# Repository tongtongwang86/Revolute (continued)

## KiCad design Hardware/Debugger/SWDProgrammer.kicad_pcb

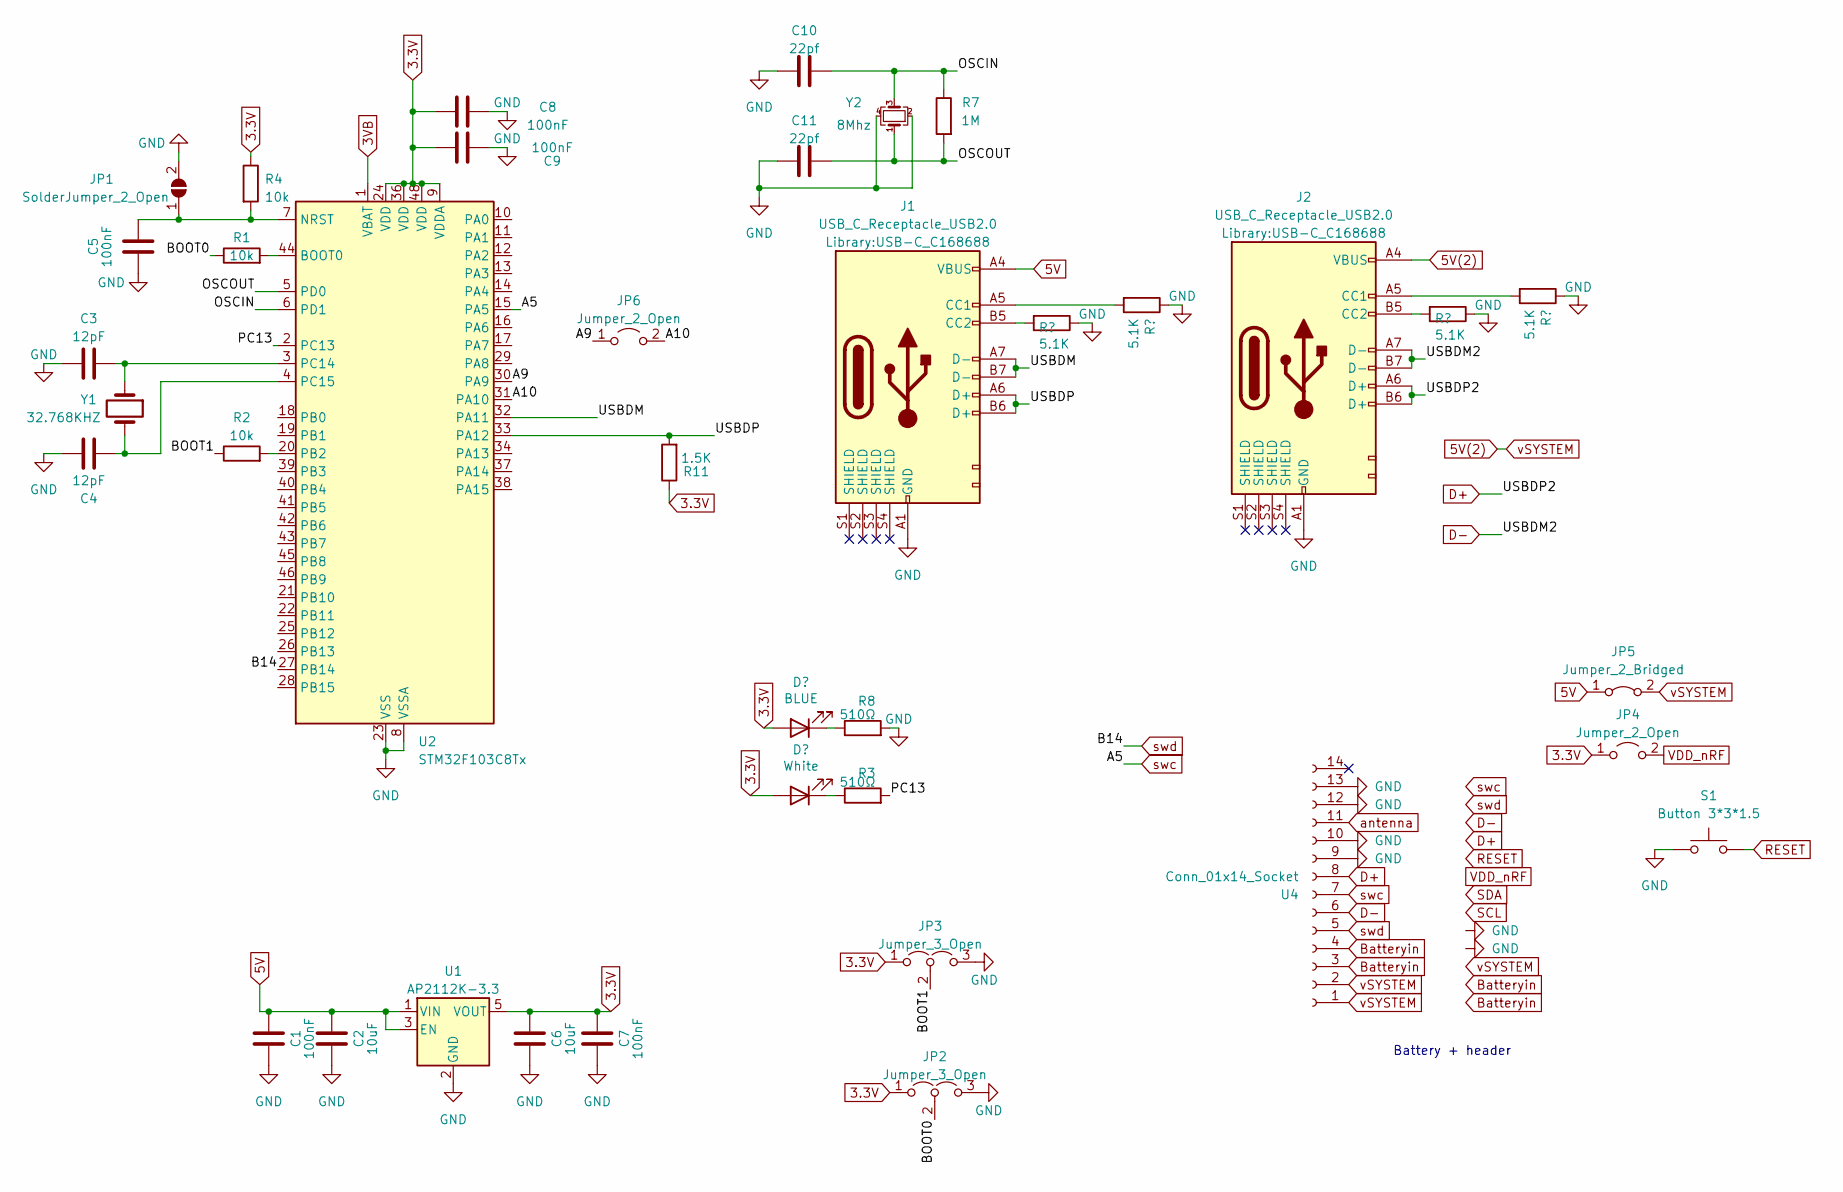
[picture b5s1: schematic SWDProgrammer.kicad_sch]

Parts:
C1, C5, C7, C8, C9: 100nF; C_0402_1005Metric
C2, C6: 10uF; C_0402_1005Metric
C3, C4: 12pF; C_0402_1005Metric
C10, C11: 22pf; C_0402_1005Metric
D1: White; LED_0402_1005Metric
D2: BLUE; LED_0402_1005Metric
J1, J2: USB_C_Receptacle_USB2.0; USB-C_C168688
JP1: SolderJumper_2_Open; SolderJumper-2_P1.3mm_Open_RoundedPad1.0x1.5mm
JP2, JP3: Jumper_3_Open; SolderJumper-3_P1.3mm_Open_RoundedPad1.0x1.5mm
JP4, JP6: Jumper_2_Open; SolderJumper-2_P1.3mm_Open_RoundedPad1.0x1.5mm
JP5: Jumper_2_Bridged; SolderJumper-2_P1.3mm_Bridged_RoundedPad1.0x1.5mm
R1, R2, R4: 10k; R_0402_1005Metric
R3, R8: 510Ω; R_0402_1005Metric
R7: 1M; R_0402_1005Metric
R9, R10, R12, R13: 5.1K; R_0402_1005Metric
R11: 1.5K; R_0402_1005Metric
S1: Button 3*3*1.5; button 3x3
U1: AP2112K-3.3; SOT-23-5
U2: STM32F103C8Tx; LQFP-48_7x7mm_P0.5mm
U4: Conn_01x14_Socket; FPC
Y1: 32.768KHZ; Crystal_SMD_3215-2Pin_3.2x1.5mm
Y2: 8Mhz; Crystal_SMD_3225-4Pin_3.2x2.5mm

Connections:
3.3V: C6.2, C7.2, C8.2, C9.2, D1.2 (A), D2.2 (A), JP2.1 (A), JP3.1 (A), JP4.1 (A), R4.1, R11.1, U1.5 (VOUT), U2.9 (VDDA), U2.24 (VDD), U2.36 (VDD), U2.48 (VDD)
3VB: U2.1 (VBAT)
5V: C1.2, C2.2, J1.A4 (VBUS), JP5.1 (A), U1.1 (VIN), U1.3 (EN); also elsewhere on the board
5V(2): J2.A4 (VBUS), JP5.2 (B), U4.1, U4.2
/BOOT0: JP2.2 (C), R1.1
/BOOT1: JP3.2 (C), R2.1
/OSCIN: C10.2, R7.1, U2.6 (PD1), Y2.3
/OSCOUT: C11.2, R7.2, U2.5 (PD0), Y2.1
/PC13: R3.2, U2.2 (PC13)
/RX: JP6.2 (B), U2.31 (PA10); also elsewhere on the board
/TX: JP6.1 (A), U2.30 (PA9); also elsewhere on the board
/USBDM: J1.A7 (D-), J1.B7 (D-), U2.32 (PA11)
/USBDP: J1.A6 (D+), J1.B6 (D+), R11.2, U2.33 (PA12)
Batteryin: U4.3, U4.4
D+: J2.A6 (D+), J2.B6 (D+), U4.8
D-: J2.A7 (D-), J2.B7 (D-), U4.6
unnamed: D1.1 (K), R3.1
unnamed: D2.1 (K), R8.1
unnamed: J1.A5 (CC1), R10.2
unnamed: J1.B5 (CC2), R9.2
unnamed: J2.A5 (CC1), R13.2
unnamed: J2.B5 (CC2), R12.2
unnamed: C5.2, JP1.1 (A), R4.2, U2.7 (NRST)
unnamed: R1.2, U2.44 (BOOT0)
unnamed: R2.2, U2.20 (PB2)
unnamed: C3.2, U2.3 (PC14), Y1.1
unnamed: C4.1, U2.4 (PC15), Y1.2
antenna: U4.11
swc: U2.15 (PA5), U4.7
swd: U2.27 (PB14), U4.5

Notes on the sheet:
Battery + header

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
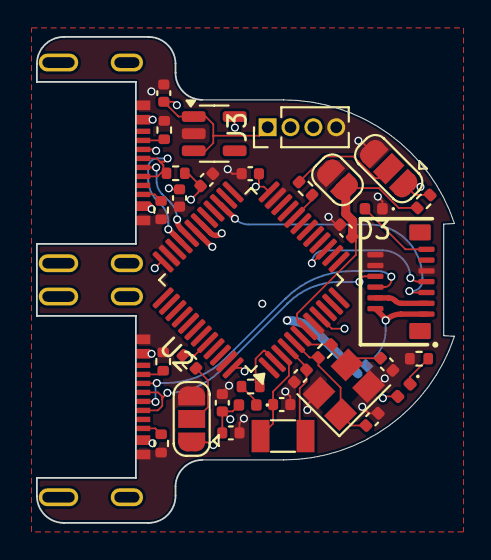
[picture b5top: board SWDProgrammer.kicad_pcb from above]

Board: 4 copper layers, 23.2 x 27.0 mm, 37 parts (1 on the bottom side), 30 nets.

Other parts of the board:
D3: White; LED_0402_1005Metric
J3: Conn_01x04_Pin; PinHeader_1x04_P1.27mm_Vertical

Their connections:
5V: J3.1; also elsewhere on the board
/RX: J3.3; also elsewhere on the board
/TX: J3.2; also elsewhere on the board

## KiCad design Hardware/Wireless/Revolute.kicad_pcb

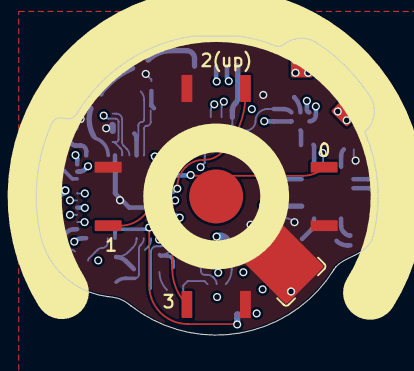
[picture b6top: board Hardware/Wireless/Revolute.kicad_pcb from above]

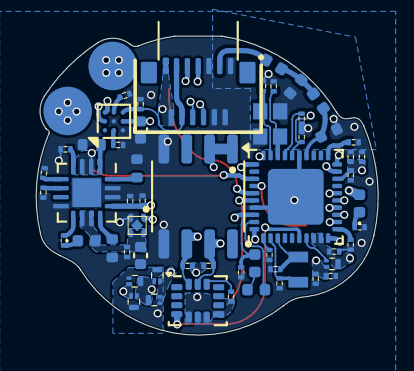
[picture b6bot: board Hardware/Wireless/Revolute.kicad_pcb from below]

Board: 4 copper layers, 19.0 x 16.6 mm, 63 parts (59 on the bottom side), 48 nets.

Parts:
C1, C6, C8: 4.7uF; Capacitor-0201
C2, C3, C16, C17: 12pF; Capacitor-0201
C4, C7, C9, C21, C22, C23, C24: 1uF; Capacitor-0201
C5, C13, C20: 100nF; Capacitor-0201
C11: 47nF; Capacitor-0201
C12: 2.2uF; Capacitor-0201
C14: 820pF; Capacitor-0201
C15: 1pF; Capacitor_0402_1005M-nosilk
C18: 100pF; Capacitor-0201
C19: 1.2pF; Capacitor_0402_1005M-nosilk
C25, C26: 10uF; C_0402_1005Metric
D1: BLUE; LED_0402_1005Metric
D2: LED; LED_0402_1005Metric
J1: -; Pogo-pin-recepticle
J2: +; Pogo-pin-recepticle
L1: 10uH; L_0402_1005Metric
L2: 15nH; L_0402_1005Metric
L3: 4.7nH; L_0402_1005Metric
L4: 2.2nH; L_0402_1005Metric
Q1: NMOS; Mosfet0402
Q2, Q3: NMOS-CSD17381F4; Mosfet0402
Q4, Q5: PMOS-CSD25483F4; Mosfet0402
R1, R11: 10k; Resistor-0201
R2, R9: 1.5k; Resistor-0201
R3: 100K; Resistor-0201
R4: 1.1k; Resistor_0402_1005M-nosilk
R5: 590; Resistor_0402_1005M-nosilk
R6, R8: 4.7K; Resistor-0201
R7, R10: 0Ω; Resistor-0201
TH1: 10K; Resistor_0402_1005M-nosilk
U1: Texas_DSBGA-9_1.62mmx1.58mm_Layout3x3_P0.5mm
U2: nrf52833_qfn40; QFN-40-1EP_5x5mm_P0.4mm_EP3.6x3.6mm
U3: AS5600; SOIC-8-1EP_3.9x4.9mm_P1.27mm_EP2.514x3.2mm
U4: MIC5504; TDFN-4
U5: BQ24075RGT; VQFN-16-1EP_3x3mm_P0.5mm_EP1.6x1.6mm
U6, U8, U9, U10: Button; SMDButton
U7: Conn_01x14_Socket; FPC
U11: LSM6DSO; LGA-14_3x2.5mm_P0.5mm_LayoutBorder3x4y
X1: 32.768 kHz; Crystal_SMD_2012-2Pin_2.0x1.2mm
X2: 32MHZ; Crystal_SMD_2016-4Pin_2.0x1.6mm

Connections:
1.8V: C12.1, U1.B3 (VDD)
BLUE_LED: D1.2 (A), U2.31 (P0.03/AIN1)
Batteryin: C4.1, U1.C3 (BAT), U7.10, U7.11
CE: R3.1, U5.4 (~CE)
D+: U2.13 (D+), U7.6
D-: U2.12 (D-), U7.8
GND: C1.1, C2.2, C3.2, C4.2, C5.2, C6.2, C7.2, C8.1, C9.2, C11.2, C12.2, C13.2, C14.1, C15.1, C16.1, C17.1, C18.1, C19.1, C20.2, C21.2, C22.2, C23.2, C24.2, C25.1, C26.2, Q2.2 (S), Q3.2 (S), R1.1, R2.1, R3.2, R4.2, R5.2, R7.1, R10.1, TH1.2, U1.B2 (VSS), U1.C1 (VSS), U2.25 (VSS), U2.37 (VSS), U2.41 (VSS), U3.4 (GND), U3.5 (PGO), U4.2 (GND), U4.5 (GND), U5.8 (VSS), U5.14 (TMR), U5.15 (SYSOFF), U5.17 (VSS), U6.2, U7.1, U7.2, U7.4, U7.5, U8.2, U9.2, U10.2, U11.6 (GND), U11.7 (GND), X2.2, X2.4
MOS_EN: Q1.1 (G), U2.7 (P0.11)
MOS_VDD: C20.1, C21.1, Q1.2 (S), R6.1, R8.1, R11.1, U3.1 (VDD5V), U3.2 (VDD3V3), U11.5 (VDDIO), U11.8 (VDD)
unnamed: C19.2, L3.2, L4.1
unnamed: D1.1 (K), R2.2
unnamed: D2.1 (K), R9.2
unnamed: J1.1, Q2.3 (D), Q3.1 (G), Q4.3 (D), Q5.1 (G)
unnamed: J2.1, Q2.1 (G), Q3.3 (D), Q4.1 (G), Q5.3 (D)
unnamed: L1.1, L2.2
unnamed: R1.2, U1.B1 (BIN)
unnamed: C15.2, L3.1, U2.24 (ANT)
unnamed: L1.2, U2.39 (DCC)
unnamed: C5.1, U2.1 (DEC1)
unnamed: C18.2, U2.27 (DEC3)
unnamed: C9.1, C11.1, L2.1, U2.26 (DEC6), U2.38 (DEC4)
unnamed: C14.2, U2.21 (DEC5)
unnamed: C8.2, U2.11 (DECUSB)
unnamed: C2.1, U2.2 (P0.00/XL1), X1.1
unnamed: C3.1, U2.3 (P0.01/XL2), X1.2
unnamed: C17.2, U2.28 (XC1), X2.1
unnamed: C16.2, U2.29 (XC2), X2.3
unnamed: R10.2, U5.6 (EN1)
unnamed: R7.2, U5.5 (EN2)
unnamed: R4.1, U5.12 (ILIM)
unnamed: R5.1, U5.16 (ISET)
unnamed: TH1.1, U5.1 (TS)
unnamed: R9.1, U5.9 (~CHG)
unnamed: R11.2, U11.12 (CS)
OUT: C22.1, C26.1, D2.2 (A), U4.3 (EN), U4.4 (VIN), U5.10 (OUT), U5.11 (OUT)
P0.15: R6.2, U1.A3 (SCL), U2.14 (P0.15), U3.7 (SCL), U11.13 (SCL)
P0.17: R8.2, U1.A2 (SDA), U2.15 (P0.17), U3.6 (SDA), U11.14 (SDA)
P0.28: U2.33 (P0.28/AIN4), U10.3
P0.29: U2.34 (P0.29/AIN5), U8.3
P0.30: U2.35 (P0.30/AIN6), U9.3
P0.31: U2.36 (P0.31/AIN7), U6.3
VBUS: C6.1, C24.1, Q4.2 (S), Q5.2 (S), U2.10 (VBUS), U5.13 (IN), U7.12, U7.13
VDD_nRF: C1.2, C7.1, C13.1, C23.1, Q1.3 (D), U2.8 (VDD), U2.9 (VDDH), U2.18 (VDD), U2.30 (VDD), U2.40 (VDD), U4.1 (VOUT)
antenna: L4.2, U7.3
int1: U2.6 (P1.09), U11.4 (INT1)
swc: U2.20 (SWDCLK), U7.7
swd: U2.19 (SWDIO), U7.9
vBAT: C25.2, U1.C2 (SRX), U5.2 (BAT), U5.3 (BAT)

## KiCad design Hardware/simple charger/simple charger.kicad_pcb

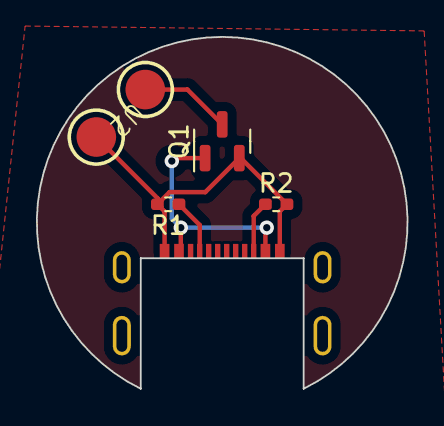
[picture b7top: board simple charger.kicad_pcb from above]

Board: 2 copper layers, 20.6 x 19.5 mm, 5 parts (0 on the bottom side), 5 nets.

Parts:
J1: USB_C_Receptacle_USB2.0; USB_C_Receptacle_XKB_U262-16XN-4BVC11
Q1: PMOS; SOT-23
R1, R2: 5.1k; R_0402_1005Metric_Pad0.72x0.64mm_HandSolder
U2: pogopins; pogopin

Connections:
GND: J1.A1 (GND), Q1.2 (G), R1.2, R2.2, U2.2 (-)
unnamed: J1.A5 (CC1), R1.1
unnamed: J1.B5 (CC2), R2.1
unnamed: Q1.3 (S), U2.1 (+)
VBUS: J1.A4 (VBUS), Q1.1 (D)

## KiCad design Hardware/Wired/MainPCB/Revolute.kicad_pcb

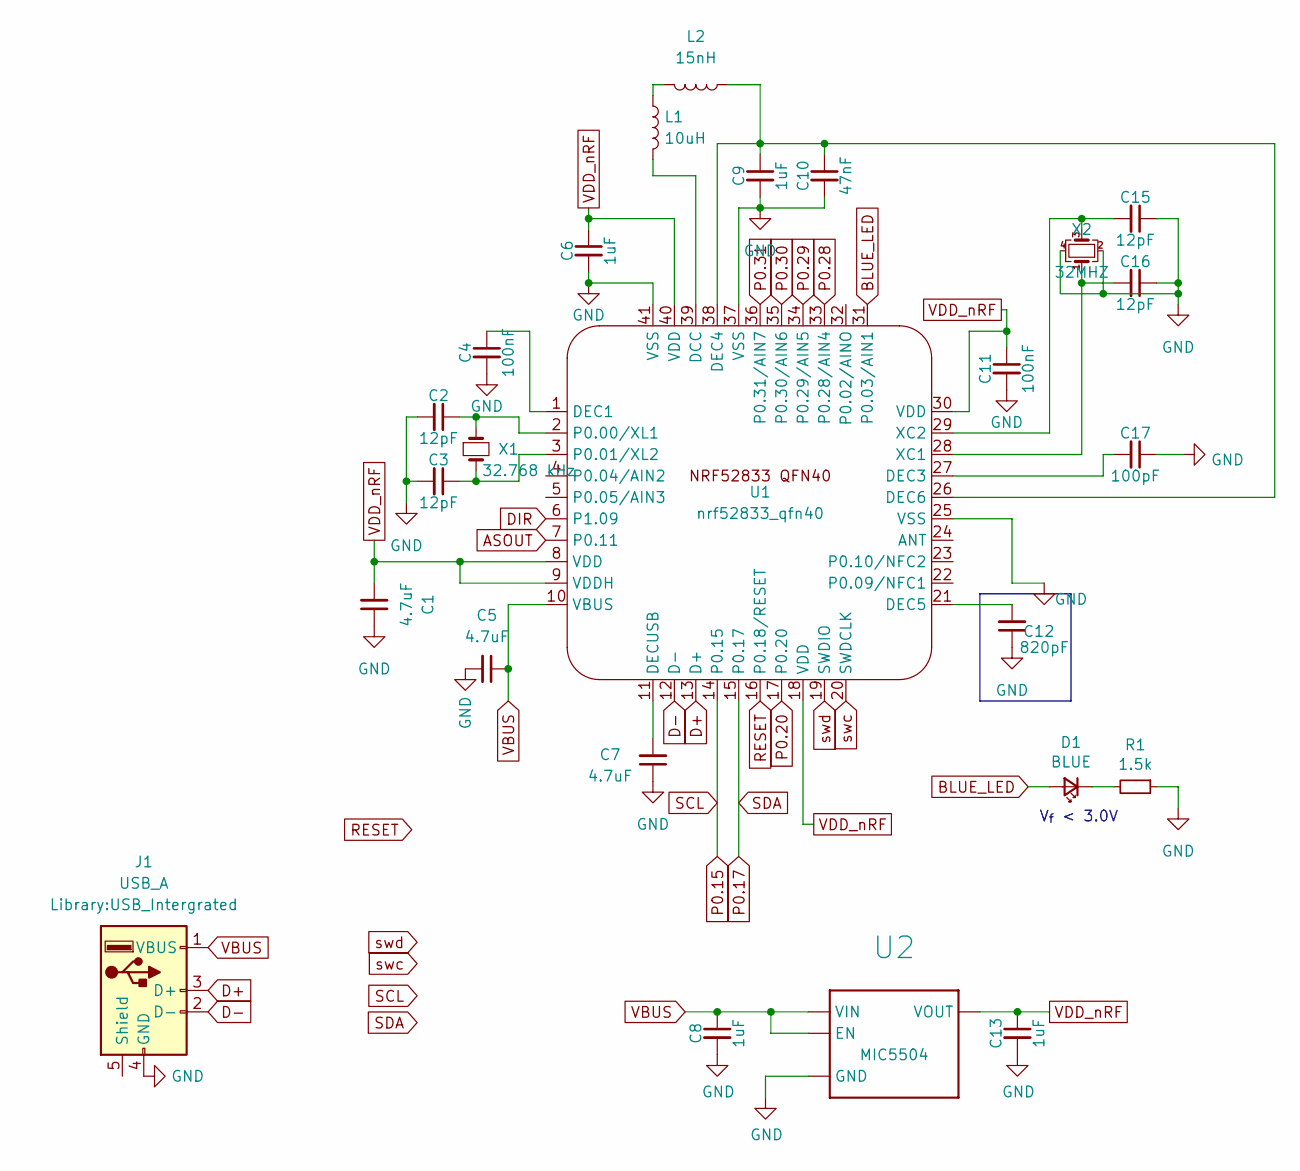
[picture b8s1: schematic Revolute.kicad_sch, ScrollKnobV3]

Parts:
C1, C5, C7: 4.7uF; Capacitor-0201
C2, C3, C15, C16: 12pF; Capacitor-0201
C4, C11: 100nF; Capacitor-0201
C6, C8, C9, C13: 1uF; Capacitor-0201
C10: 47nF; Capacitor-0201
C12: 820pF; Capacitor-0201
C17: 100pF; Capacitor-0201
D1: BLUE; LED_0402_1005Metric
J1: USB_A; USB_Intergrated
L1: 10uH; L_0402_1005Metric
L2: 15nH; L_0402_1005Metric
R1: 1.5k; Resistor_0402_1005M-nosilk; Manufacturer Part RC0402FR-071K5L; LCSC Part C114759
U1: nrf52833_qfn40; QFN-40-1EP_5x5mm_P0.4mm_EP3.6x3.6mm
U2: MIC5504; TDFN-4
X1: 32.768 kHz; Crystal_SMD_2012-2Pin_2.0x1.2mm
X2: 32MHZ; Crystal_SMD_2016-4Pin_2.0x1.6mm

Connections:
ASOUT: U1.7 (P0.11)
BLUE_LED: D1.2 (A), U1.31 (P0.03/AIN1)
D+: J1.3 (D+), U1.13 (D+)
D-: J1.2 (D-), U1.12 (D-)
DIR: U1.6 (P1.09)
GND: C1.1, C2.2, C3.2, C4.2, C5.2, C6.2, C7.1, C8.2, C9.2, C10.2, C11.2, C12.1, C13.2, C15.1, C16.1, C17.1, J1.4 (GND), R1.1, U1.25 (VSS), U1.37 (VSS), U1.41 (VSS), U2.2 (GND), U2.5 (GND), X2.2, X2.4
unnamed: D1.1 (K), R1.2
unnamed: L1.1, L2.2
unnamed: L1.2, U1.39 (DCC)
unnamed: C4.1, U1.1 (DEC1)
unnamed: C17.2, U1.27 (DEC3)
unnamed: C9.1, C10.1, L2.1, U1.26 (DEC6), U1.38 (DEC4)
unnamed: C12.2, U1.21 (DEC5)
unnamed: C7.2, U1.11 (DECUSB)
unnamed: C2.1, U1.2 (P0.00/XL1), X1.1
unnamed: C3.1, U1.3 (P0.01/XL2), X1.2
unnamed: C16.2, U1.28 (XC1), X2.1
unnamed: C15.2, U1.29 (XC2), X2.3
P0.15: U1.14 (P0.15)
P0.17: U1.15 (P0.17)
P0.20: U1.17 (P0.20)
P0.28: U1.33 (P0.28/AIN4)
P0.29: U1.34 (P0.29/AIN5)
P0.30: U1.35 (P0.30/AIN6)
P0.31: U1.36 (P0.31/AIN7)
RESET: U1.16 (P0.18/RESET)
VBUS: C5.1, C8.1, J1.1 (VBUS), U1.10 (VBUS), U2.3 (EN), U2.4 (VIN)
VDD_nRF: C1.2, C6.1, C11.1, C13.1, U1.8 (VDD), U1.9 (VDDH), U1.18 (VDD), U1.30 (VDD), U1.40 (VDD), U2.1 (VOUT)
swc: U1.20 (SWDCLK)
swd: U1.19 (SWDIO)

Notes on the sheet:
V_{f} < 3.0V

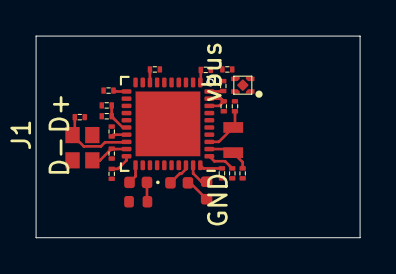
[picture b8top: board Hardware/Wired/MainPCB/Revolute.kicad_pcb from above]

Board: 4 copper layers, 18.0 x 11.2 mm, 25 parts (0 on the bottom side), 18 nets.

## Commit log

2022-10-10 Uploaded files
    Uploaded -PCB -3D Print -UF2 -Bootloader
2022-10-10 Added pictures
2022-10-10 Added New Pictures
2022-10-10 added even more pictures
2022-10-10 added 1 new uf2 file
2022-10-10 moved pictures
2022-10-10 remove picture
2022-10-10 Removed pic
2022-10-12 Added section-analysis pic
2022-12-04 Added license
2022-12-04 updated formatting of pictures
2023-05-05 updated to kicad 7
2023-05-05 version 2 base pcb
2023-05-05 Added V2 images, v2 pcb, v2 top pcb, v2 3d files
2023-05-05 updated files
2023-06-21 sorted files, added source code for v2
2023-06-21 app base config
2023-06-22 hid tess
2023-06-22 hidtest
2023-06-24 hid sample works
2023-06-24 fixed app again
2023-06-24 app now emulates function of encoder
2023-06-24 app works but skips at high speed
2023-06-27 sync
2023-06-28 updated pcb design
2023-06-28 made pcb smaller
2023-06-28 export step
2023-06-28 v2 magnet snapping update
2023-06-30 added 3d visualization files
2023-07-05 3d files for all versions
2023-07-07 app fixing progress
2023-07-08 got threads and semaphore working
2023-07-08 works
2023-07-08 idents snap in middle of magnet
2023-07-08 clean up code
2023-07-08 added scroll direction
2023-07-08 removed console
2023-07-08 edited readme
2023-07-23 better preforming code v2
2023-11-20 git ignore, 3d files
2023-11-27 modified 3d print files
2023-11-27 updated gerbers
2023-11-27 added gerberzip
2023-11-27 modified connector gerber
2023-11-28 updated ibom
2023-12-02 edited software
2023-12-04 added precompiled uf2
2023-12-11 added bootloader source files
2023-12-12 modified gerber
2023-12-27 added revolute wireless(work in progress)
2023-12-27 worked on wireless
2023-12-28 added debug board (work in progress)
2023-12-29 worked on debugger, has to be flipped
2023-12-30 finished debugger and wireless
2024-01-01 exported gerbers
2024-01-02 update ibom
2024-01-02 changed via hole sizes
2024-01-08 fixed problems on debugger
2024-01-13 fixed design
2024-01-14 added pogo charging pins, fixed debug connector
2024-01-25 fixed some non existant bugs
2024-01-25 updated gerbers and bom
2024-02-01 fixed usb datapin issue
2024-02-01 build revolute wireless bootloader and first firmware
2024-02-02 worked on software, fixed wireless pcb power path circuit
2024-02-03 fixed debugger datapin board, connected dir and out of as5600 to mcu
2024-02-07 edited debugger board, generated new gerbers
2024-02-08 revised wireless design
2024-02-09 enabled console over cdc acm, changed bluetooth advertizement infornmation
2024-02-21 implemented 4button design
2024-02-24 new gerbers
2024-02-24 revopod kikad files
    suck my dynamite dick
2024-03-01 updated to kicad 8
2024-03-03 migrated debugger to kicad 8
2024-03-03 simple charger for revolute
2024-03-17 modified wireless PCB
2024-03-26 modified battery ground pad
2024-04-10 deleted old files for revopod
2024-04-10 revopod v1 prototype files
    deleted the previous version and replaced it with this v1 version
2024-04-12 modified pcb files
2024-04-17 added testing pads to depricate fpc connector
2024-04-26 added ID column
2024-06-01 migrated components to 0201
2024-06-02 refined pcb
2024-06-19 updated pcb 0201 components and flex battery attachment
2024-06-19 new debugger
2024-07-27 current version
2024-08-18 added gyro, flex pcb antenna
2024-09-15 revision 3, added mosfets for sensor power cutoff
2024-10-19 changed board shape, adedd unrouted test board, added active rectifier for reverse polarity, changed fuel gauge ic to smaller
2024-12-22 Update LICENCE
2024-12-27 new flex and new pcbs
2024-12-27 changed name of beacon sample folder
2024-12-29 added jlink adapter
2024-12-29 added status led
2025-02-14 revolute production boards
2025-02-17 Backlink to CADLAB.io has been added.
2025-02-17 unrouted test board
2025-02-17 added copper zone keep out for antenna
2025-02-17 remove non test board files
2025-02-17 removed more files
2025-02-17 routing session 1
2025-02-21 added TLV493D sensor
2025-02-21 route2
2025-02-21 new route
2025-02-21 route
2025-02-21 added some zones
2025-02-22 routed
2025-02-22 test board done
2025-02-24 finished routing
2025-02-25 centered flex pcb, made pcb 1.6mm
2025-02-27 added files back
2025-03-11 update kicad 9
2025-03-11 kicad 9
2025-10-09 added new refined board
2025-12-29 test board
